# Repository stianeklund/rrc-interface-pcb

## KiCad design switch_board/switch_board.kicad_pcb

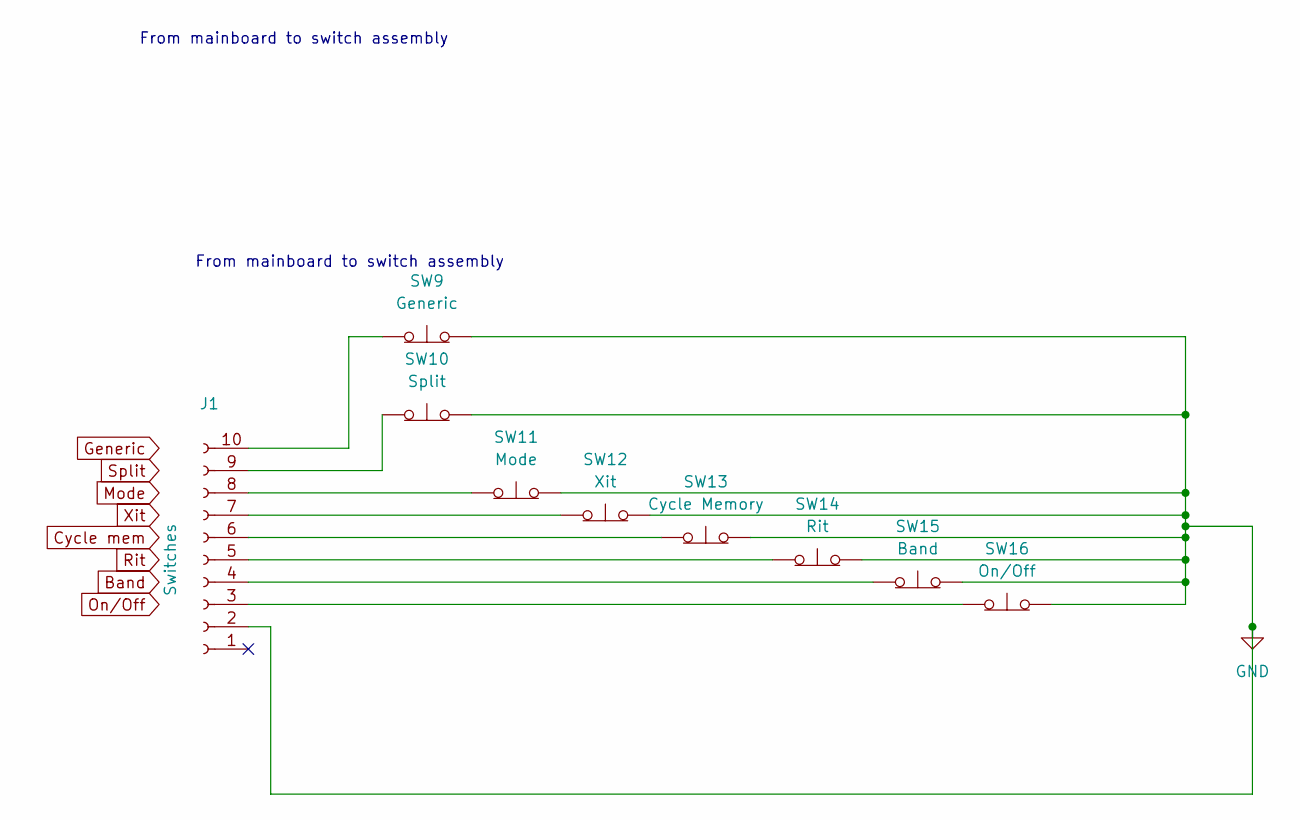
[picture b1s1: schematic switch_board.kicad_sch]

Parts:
J1: Switches; JST_XH_B10B-XH-AM_1x10_P2.50mm_Vertical
SW9: Generic; SW_Cherry_MX_1.00u_Plate
SW10: Split; SW_Cherry_MX_1.00u_PCB
SW11: Mode; SW_Cherry_MX_1.00u_PCB
SW12: Xit; SW_Cherry_MX_1.00u_PCB
SW13: Cycle Memory; SW_Cherry_MX_1.00u_PCB
SW14: Rit; SW_Cherry_MX_1.00u_PCB
SW15: Band; SW_Cherry_MX_1.00u_PCB
SW16: On/Off; SW_Cherry_MX_1.00u_PCB

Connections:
GND: J1.2, SW9.2 (B), SW10.2 (B), SW11.2 (B), SW12.2 (B), SW13.2 (B), SW14.2 (B), SW15.2 (B), SW16.2 (B)
unnamed: J1.3, SW16.1 (A)
unnamed: J1.4, SW15.1 (A)
unnamed: J1.5, SW14.1 (A)
unnamed: J1.6, SW13.1 (A)
unnamed: J1.7, SW12.1 (A)
unnamed: J1.8, SW11.1 (A)
unnamed: J1.9, SW10.1 (A)
unnamed: J1.10, SW9.1 (A)

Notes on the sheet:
From mainboard to switch assembly

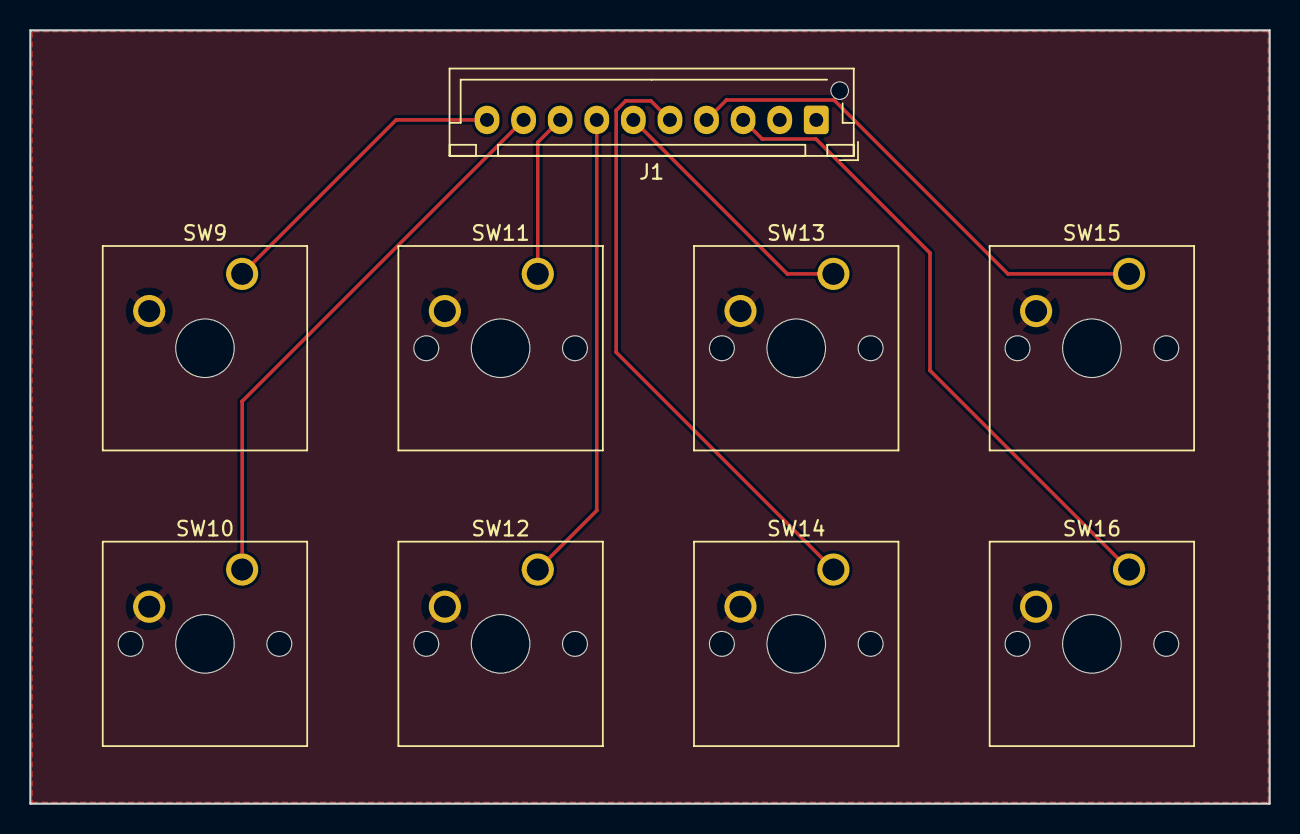
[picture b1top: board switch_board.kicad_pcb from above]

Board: 2 copper layers, 84.7 x 52.8 mm, 9 parts (0 on the bottom side), 9 nets.

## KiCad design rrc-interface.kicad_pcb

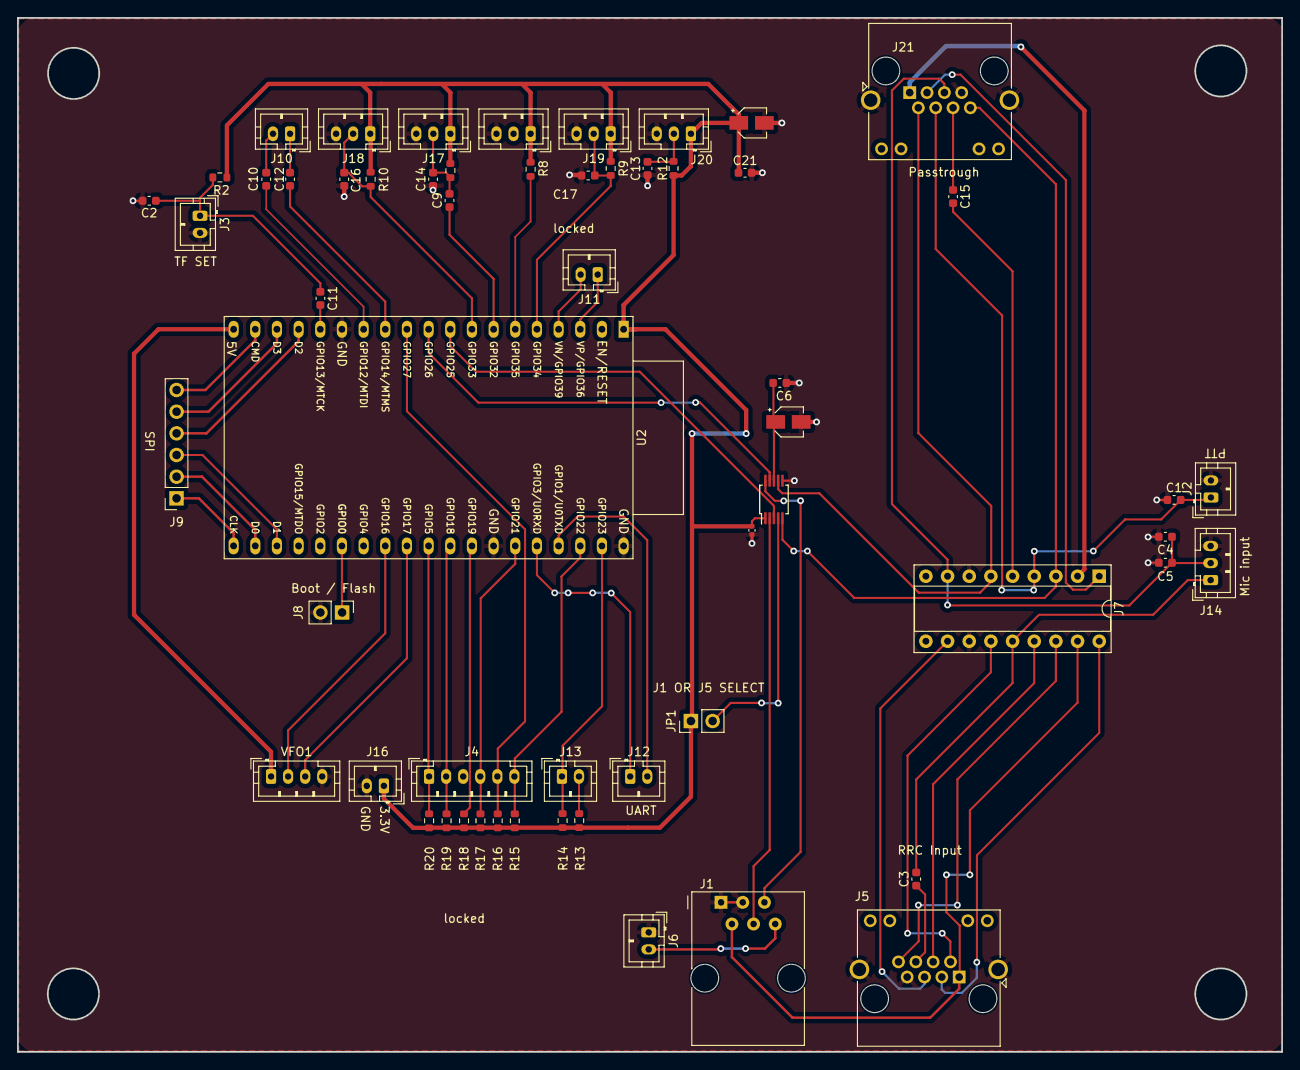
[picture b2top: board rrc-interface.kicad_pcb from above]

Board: 2 copper layers, 148.2 x 121.2 mm, 58 parts (0 on the bottom side), 50 nets.

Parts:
C1, C2, C3, C6, C9, C10, C11, C12, C13, C14, C15, C16, C17, C21: 0.1uF; C_0603_1608Metric
C4: 0.1 uF; C_0603_1608Metric
C5: 330 pF; C_0603_1608Metric
C7, C20: 10 uF; CP_Elec_3x5.3
C8: 0.1uF; C_0402_1005Metric
J1: 6P6C RRC; RJ12_Amphenol_54601
J2: Ptt; JST_PH_B2B-PH-K_1x02_P2.00mm_Vertical
J3: TF Set; JST_PH_B2B-PH-K_1x02_P2.00mm_Vertical
J4: Conn_01x06; JST_PH_B6B-PH-K_1x06_P2.00mm_Vertical
J5: To RRC; RJ45_Amphenol_RJHSE538X
J6: Audio Output; JST_PH_B2B-PH-K_1x02_P2.00mm_Vertical
J7: RRC Optional Config DIP Socket; DIP-18_W7.62mm_Socket
J8: Flash mode; PinHeader_1x02_P2.54mm_Vertical
J9: SPI Breakout; PinSocket_1x06_P2.54mm_Vertical
J10, J11: Input Only Pins; JST_PH_B2B-PH-K_1x02_P2.00mm_Vertical
J12: UART Socket; JST_PH_B2B-PH-K_1x02_P2.00mm_Vertical
J13: Conn_01x02; JST_PH_B2B-PH-K_1x02_P2.00mm_Vertical
J14: Mic input; JST_PH_B3B-PH-K_1x03_P2.00mm_Vertical
J15: Rit Xit Value; JST_PH_B3B-PH-K_1x03_P2.00mm_Vertical
J16: 3V & GND; JST_PH_B2B-PH-K_1x02_P2.00mm_Vertical
J17: RF Gain; JST_PH_B3B-PH-K_1x03_P2.00mm_Vertical
J18: AF Gain; JST_PH_B3B-PH-K_1x03_P2.00mm_Vertical
J19: IF Shift; JST_PH_B3B-PH-K_1x03_P2.00mm_Vertical
J20: Spare; JST_PH_B3B-PH-K_1x03_P2.00mm_Vertical
J21: Passthrough; RJ45_Amphenol_RJHSE538X
JP1: Jumper_2_Open; PinHeader_1x02_P2.54mm_Vertical
R2, R8, R9, R10, R11, R12, R13, R14, R15, R16, R17, R18, R19, R20: 2.2K; R_0603_1608Metric
U1: ADG884xRM; MSOP-10_3x3mm_P0.5mm
U2: ESP32-DevKitC
VFO1: Magnetic Rotary Encoder; JST_PH_B4B-PH-K_1x04_P2.00mm_Vertical

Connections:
+3.3V: C8.2, C20.1, C21.1, J15.1, J16.1, J17.1, J18.1, J19.1, J20.1, JP1.1 (A), R2.2, R8.1, R9.1, R10.1, R11.1, R12.1, R13.1, R14.1, R15.1, R16.1, R17.1, R18.1, R19.1, R20.1, U1.1 (VDD), U2.1 (3V3)
+5V: U2.19 (5V), VFO1.1 (3.3V)
/AF Gain: C16.1, J18.2, R10.2, U2.8 (32K_XN/GPIO33/ADC1_CH5)
/Boot / Flash: J8.1, U2.25 (GPIO0/BOOT/ADC2_CH1)
/CMD: J9.6, U2.18 (CMD)
/Encoder A: U2.28 (GPIO17), VFO1.3 (A)
/Encoder B: U2.27 (GPIO16), VFO1.2 (B)
/GPIO 12: C10.1, J10.2
/GPIO 14: C12.1, J10.1
/GPIO 36: J11.1, U2.3 (SENSOR_VP/GPIO36/ADC1_CH0)
/GPIO 39: J11.2, U2.4 (SENSOR_VN/GPIO39/ADC1_CH3)
/IF Shift: C17.1, J19.2, R9.2, U2.5 (VDET_1/GPIO34/ADC1_CH6)
/RDO: J1.4, U1.2 (S1A), U1.3 (D1), U2.9 (DAC_1/ADC2_CH8/GPIO25)
/RF Gain: C9.2, C14.1, J17.2, R11.2
/RX: J12.2, U2.35 (U0TXD/GPIO1)
/Rit/Xit Value: J15.2, R8.2, U2.6 (VDET_2/GPIO35/ADC1_CH7)
/SD_CLK: J9.1, U2.20 (SD_CLK/GPIO6)
/SD_DATA0: J9.2, U2.21 (SD_DATA0/GPIO7)
/SD_DATA1: J9.3, U2.22 (SD_DATA1/GPIO8)
/SD_DATA2: J9.4, U2.16 (SD_DATA2/GPIO9)
/SD_DATA3: J9.5, U2.17 (SD_DATA3/GPIO10)
/Spare: C13.1, J20.2, R12.2
/TDO: J1.5, U1.9 (D2), U1.10 (S2A), U2.10 (DAC_2/ADC2_CH9/GPIO26)
/TX: J12.1, U2.34 (U0RXD/GPIO3)
AF: J1.6, J6.2
Band: J13.1, R14.2, U2.37 (GPIO23)
Cycle mem: J4.5, R16.2, U2.11 (ADC2_CH7/GPIO27)
GND: C1.1, C2.2, C4.2, C5.2, C6.1, C7.2, C8.1, C13.2, C14.2, C16.2, C17.2, C20.2, C21.2, J1.1, J1.3, J2.2, J3.2, J5.7, J5.SH, J6.1, J7.7 (GND), J7.12 (GND), J8.2, J14.3, J15.3, J16.2, J17.3, J18.3, J19.3, J20.3, J21.7, J21.SH, U1.6 (GND), U2.14 (GND), U2.32 (GND), U2.38 (GND), VFO1.4 (GND)
Generic: J4.1, R20.2, U2.29 (GPIO5)
MIC: C3.2, C15.2, J7.5 (MIC), J7.14 (MIC), J14.1
MICE: C4.1, C5.1, J5.5, J7.8 (MICE), J7.11 (MICE), J14.2, J21.5
Mode: J4.3, R18.2, U2.31 (GPIO19)
unnamed: C3.1, J5.6
unnamed: C15.1, J21.6
unnamed: C6.2, C7.1, JP1.2 (B), U1.4 (IN1), U1.8 (IN2)
unnamed: C9.1, U2.7 (32K_XP/GPIO32/ADC1_CH4)
unnamed: C11.2, U2.15 (MTCK/GPIO13/ADC2_CH4)
unnamed: C10.2, U2.13 (MTDI/GPIO12/ADC2_CH5)
unnamed: C12.2, U2.12 (MTMS/GPIO14/ADC2_CH6)
On/Off: J13.2, R13.2
PTT: C1.2, J2.1, J5.4, J7.4 (PWR_ON_SW), J7.15 (PWR_ON_SW), J21.4
PWR 8V: J1.2, J5.1, J7.2 (PWR_(8/9V)), J7.17 (PWR_(8/9V)), J21.1
PWR SW: J7.9 (NC), J7.10 (NC)
RXD: J5.8, J7.3 (RXD), J7.16 (RXD), J21.8, U1.5 (S1B)
Rit: J4.6, R15.2, U2.36 (GPIO22)
SPK OUT: J5.3, J7.1 (SPK_OUT), J7.18 (SPK_OUT), J21.3
Split: J4.2, R19.2, U2.30 (GPIO18)
TF Set: C2.1, C11.1, J3.1, R2.1
TXD: J5.2, J7.6 (TXD), J7.13 (TXD), J21.2, U1.7 (S2B)
Xit: J4.4, R17.2, U2.33 (GPIO21)

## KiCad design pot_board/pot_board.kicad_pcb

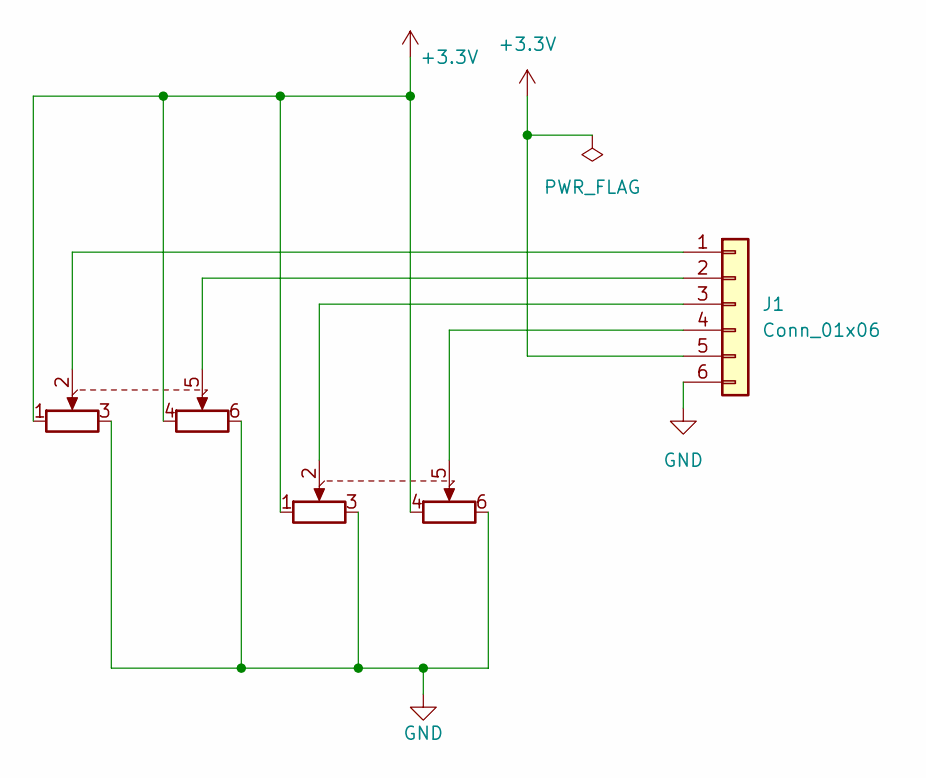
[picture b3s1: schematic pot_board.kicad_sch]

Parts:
J1: Conn_01x06; JST_XH_B6B-XH-A_1x06_P2.50mm_Vertical
RV1, RV2: R_Potentiometer_Dual; Potentiometer_Alps_RK097_Dual_Horizontal

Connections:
+3.3V: J1.5, RV1.1, RV1.4, RV2.1, RV2.4
GND: J1.6, RV1.3, RV1.6, RV2.3, RV2.6
unnamed: J1.1, RV1.2
unnamed: J1.2, RV1.5
unnamed: J1.3, RV2.2
unnamed: J1.4, RV2.5

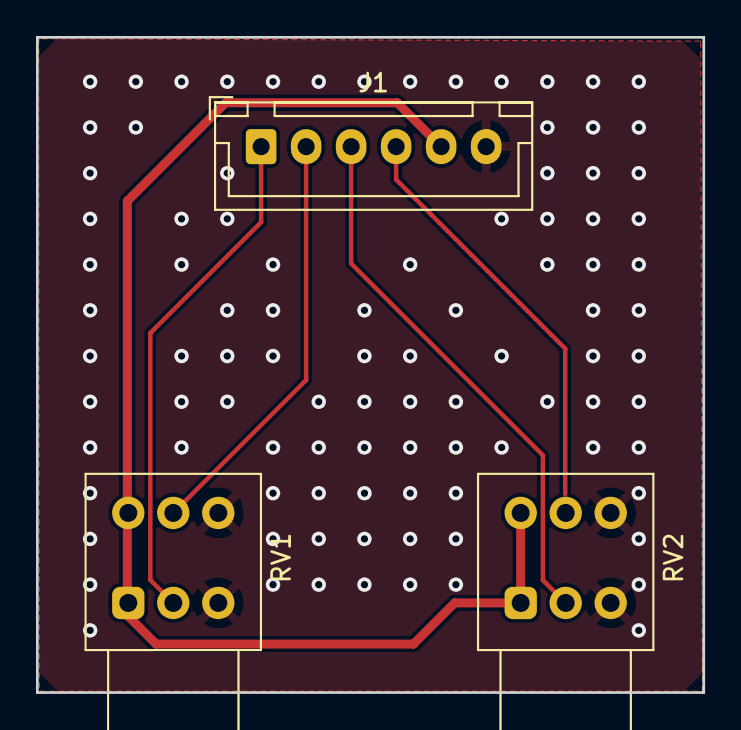
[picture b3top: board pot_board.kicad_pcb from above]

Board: 2 copper layers, 37.0 x 36.4 mm, 3 parts (0 on the bottom side), 6 nets.

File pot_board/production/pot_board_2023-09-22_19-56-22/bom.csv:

Designator,Footprint,Quantity,Value,LCSC Part #
J1,JST_XH_B6B-XH-A_1x06_P2.50mm_Vertical,1,Conn_01x06,
"RV1, RV2",Potentiometer_Alps_RK097_Dual_Horizontal,2,R_Potentiometer_Dual,

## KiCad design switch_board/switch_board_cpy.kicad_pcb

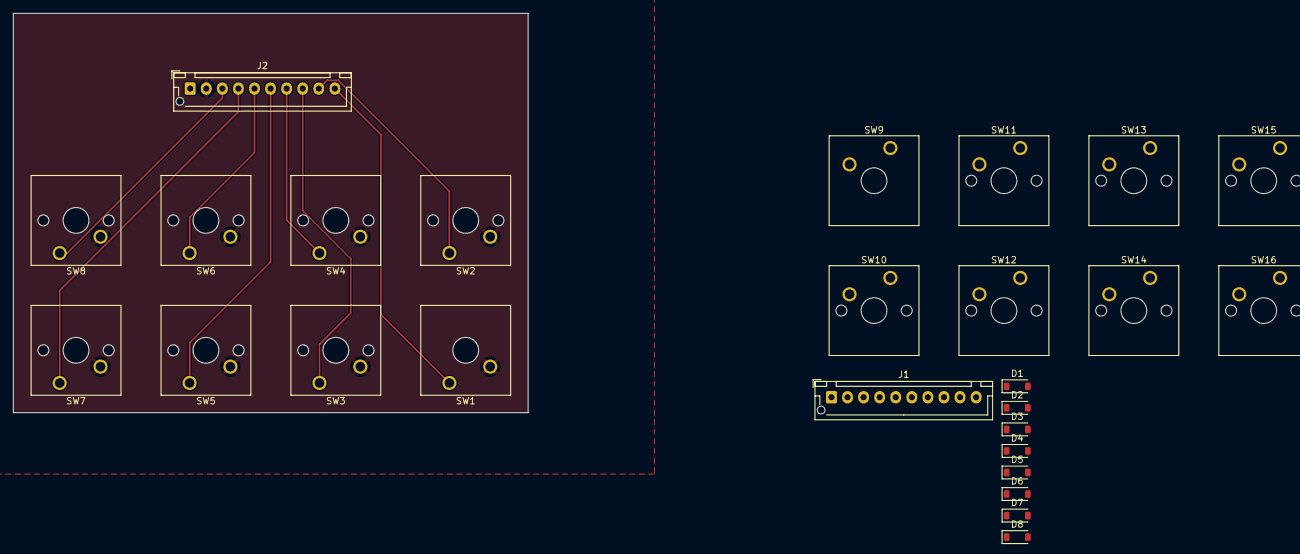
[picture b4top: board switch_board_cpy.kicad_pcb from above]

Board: 2 copper layers, 80.0 x 62.1 mm, 26 parts (0 on the bottom side), 23 nets.

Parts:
D1, D2, D3, D4, D5, D6, D7, D8: 1N4148W; D_SOD-123
J1, J2: Switches; JST_XH_B10B-XH-AM_1x10_P2.50mm_Vertical
SW1, SW9: Generic; SW_Cherry_MX_1.00u_Plate
SW2, SW10: Split; SW_Cherry_MX_1.00u_PCB
SW3, SW11: Mode; SW_Cherry_MX_1.00u_PCB
SW4, SW12: Xit; SW_Cherry_MX_1.00u_PCB
SW5, SW13: Cycle Memory; SW_Cherry_MX_1.00u_PCB
SW6, SW14: Rit; SW_Cherry_MX_1.00u_PCB
SW7, SW15: Band; SW_Cherry_MX_1.00u_PCB
SW8, SW16: On/Off; SW_Cherry_MX_1.00u_PCB

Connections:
GND: J1.2, SW9.2 (B), SW10.2 (B), SW11.2 (B), SW12.2 (B), SW13.2 (B), SW14.2 (B), SW15.2 (B), SW16.2 (B)
unnamed: D1.2 (A), SW1.2
unnamed: D1.1 (K), D2.1 (K), D3.1 (K), D4.1 (K), J2.5
unnamed: D2.2 (A), SW2.2
unnamed: D3.2 (A), SW3.2
unnamed: D4.2 (A), SW4.2
unnamed: D5.2 (A), SW5.2
unnamed: D5.1 (K), D6.1 (K), D7.1 (K), D8.1 (K), J2.6
unnamed: D6.2 (A), SW6.2
unnamed: D7.2 (A), SW7.2
unnamed: D8.2 (A), SW8.2
unnamed: J1.3, SW16.1 (A)
unnamed: J1.4, SW15.1 (A)
unnamed: J1.5, SW14.1 (A)
unnamed: J1.6, SW13.1 (A)
unnamed: J1.7, SW12.1 (A)
unnamed: J1.8, SW11.1 (A)
unnamed: J1.9, SW10.1 (A)
unnamed: J1.10, SW9.1 (A)
unnamed: J2.1, SW1.1, SW5.1
unnamed: J2.2, SW2.1, SW6.1
unnamed: J2.3, SW3.1, SW7.1
unnamed: J2.4, SW4.1, SW8.1

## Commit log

2023-09-08 add separate board for potentiometers
    for AF gain / RF gain etc..
    Connects to the main board and uses the onboard ADC's on the esp32
2023-09-08 add speaker / ptt board prototype
    Not sure if this is really needed anymore with the design changes of the main board
2023-09-08 add rrc interface mainboard proto
2023-09-08 add switch daugtherboard
2023-09-18 cont routing work
    Changes:
    * Added mounting holes
    * Tried to trim down PCB size a litle more.
    * Attempted to separate digital IO from analog.
    * Added socket IC for RJ45 & 6P6C / RJ12 configurability.
    * WIP: Add muxer for UART line switching.
2023-09-20 add gnd pour to top layer, try to optimize routing
    Changes:
    * Opt to use normal via's instead of micro via's to reduce cost / production time.
    * Add ground pour / plane to top layer.
    * Reorganize component layout a bit to try to optimize paths.
    * Change connector types to JST (will soon have a crimp kit for these connectors).
    * Try to split the PCB into analog and digital sections.
2023-09-30 update main board routing, add 3d models and improve layout
    Changes:
    * update main board layout a bit
    * try to improve routing
    * add 3d model for 6p6c
    * add decoupling caps to ptt line
    * almost finish pot board
2023-10-05 cont work on boards
